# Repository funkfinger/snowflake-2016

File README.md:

# snowflake-2016
An ATtiny based snowflake ornament. Happy Holidays friends...

### Board shape
  * created the board in Illustrator and added extra points (`Object -> Path -> Add Anchor Points`).
  * exported shape as `DXF` - settings:
    * R13/LT95
    * scale - 1mm = 1 unit
    * colors 256 - PNG
    * max editabitity
    * export selected art only
  * import shape using `import_dxf_polygons_v4.ulp` ([found here](https://raw.githubusercontent.com/todbot/eagle-tricks/master/import_dxf_polygons_v4.ulp)) - settings:
    * scale 1
    * import to layer: 20 - dimension
    * wire or polygon: wire
    * pen width: .2
  * make sure shape is 'watertight' - had to clean up small space on snowflake in Eagle by drawing a 'wire' to close.

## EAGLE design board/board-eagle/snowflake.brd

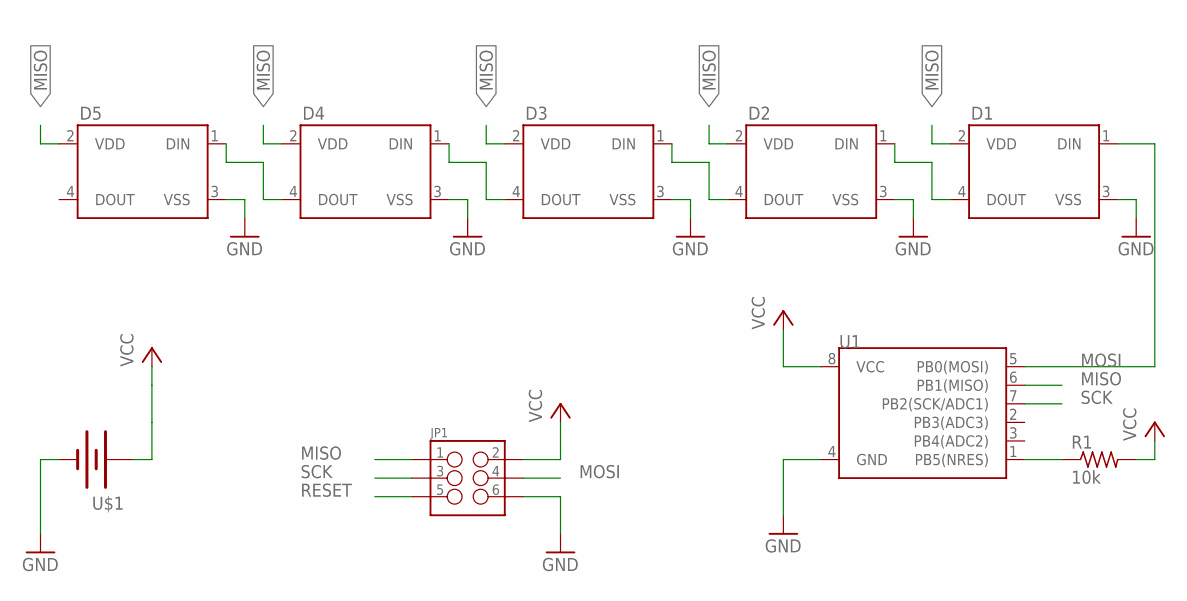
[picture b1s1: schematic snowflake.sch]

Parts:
D1, D2, D3, D4, D5: WS2812BEDGE_MOUNT_5MM_LED; WS2812B
JP1: M03X2POGO_PINS; 2X3_POGO
R1: 10k; R0805
U1: ATTINY45TINY85-20-SMT; SO08-EIAJ
U$1: BATTERY; BHX2-2032-SM

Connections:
GND: D1.3 (VSS), D2.3 (VSS), D3.3 (VSS), D4.3 (VSS), D5.3 (VSS), JP1.P$6 (6), U1.4 (GND), U$1.GND (-)
MISO: D1.2 (VDD), D2.2 (VDD), D3.2 (VDD), D4.2 (VDD), D5.2 (VDD), JP1.P$1 (1), U1.6 (PB1(MISO))
MOSI: D1.1 (DIN), JP1.P$4 (4), U1.5 (PB0(MOSI))
unnamed: D1.4 (DOUT), D2.1 (DIN)
unnamed: D2.4 (DOUT), D3.1 (DIN)
unnamed: D3.4 (DOUT), D4.1 (DIN)
unnamed: D4.4 (DOUT), D5.1 (DIN)
RESET: JP1.P$5 (5), R1.1, U1.1 (PB5(NRES))
SCK: JP1.P$3 (3), U1.7 (PB2(SCK/ADC1))
VCC: JP1.P$2 (2), R1.2, U1.8 (VCC), U$1.VCC (+), U$1.VCC-2 (+)

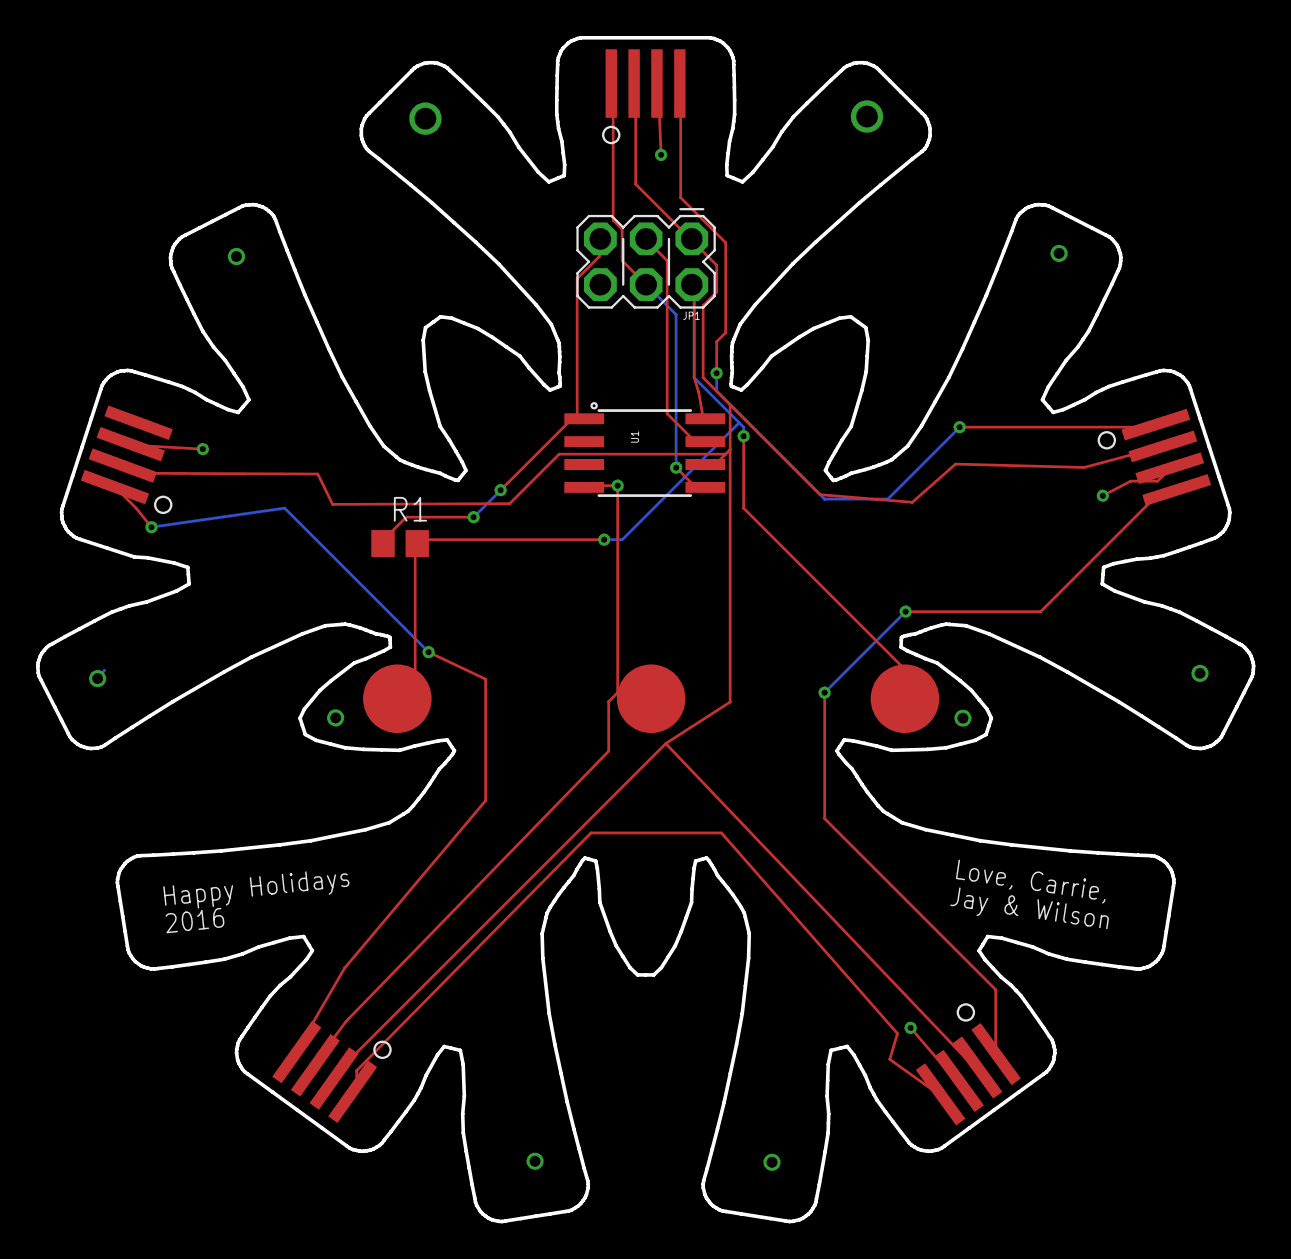
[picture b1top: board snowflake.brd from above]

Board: 2 copper layers, 67.5 x 65.8 mm, 9 parts (0 on the bottom side), 10 nets.

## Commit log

2016-11-26 adding board in illustrator
2016-11-26 update board in illustrator
2016-11-28 board design
2016-11-30 code start
2016-12-14 new board and zip
2017-01-14 final?

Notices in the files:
parts and their libraries:
SparkFun-Connectors: Licensing: Creative Commons ShareAlike 4.0 International - https://creativecommons.org/licenses/by-sa/4.0
